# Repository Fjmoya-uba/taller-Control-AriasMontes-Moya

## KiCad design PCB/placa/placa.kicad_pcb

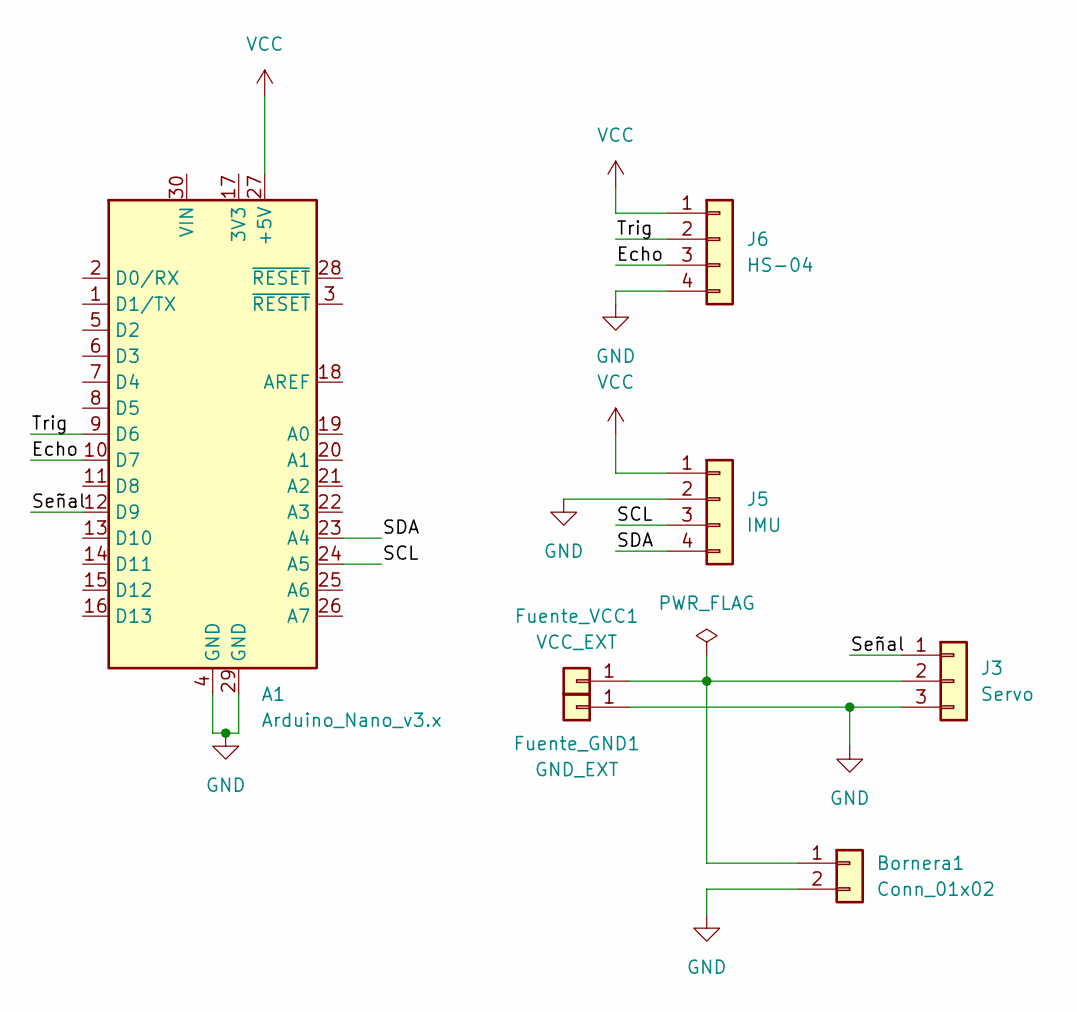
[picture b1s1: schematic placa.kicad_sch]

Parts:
A1: Arduino_Nano_v3.x; Arduino_Nano
Bornera1: Conn_01x02; TerminalBlock_Phoenix_MKDS-1,5-2-5.08_1x02_P5.08mm_Horizont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
Fuente_GND1: GND_EXT; PinHeader_1x01_P2.54mm_Vertical
Fuente_VCC1: VCC_EXT; PinHeader_1x01_P2.54mm_Vertical
J3: Servo; PinHeader_1x03_P2.54mm_Vertical
J5: IMU; PinHeader_1x04_P2.54mm_Vertical
J6: HS-04; PinHeader_1x04_P2.54mm_Vertical

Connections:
/Echo: A1.10 (D7), J6.3
/SCL: A1.24 (A5), J5.3
/SDA: A1.23 (A4), J5.4
/Señal: A1.12 (D9), J3.1
/Trig: A1.9 (D6), J6.2
GND: A1.4 (GND), A1.29 (GND), Bornera1.2, Fuente_GND1.1 (Pin_1_1), J3.3, J5.2, J6.4
unnamed: Bornera1.1, Fuente_VCC1.1 (Pin_1_1), J3.2
VCC: A1.27 (+5V), J5.1, J6.1

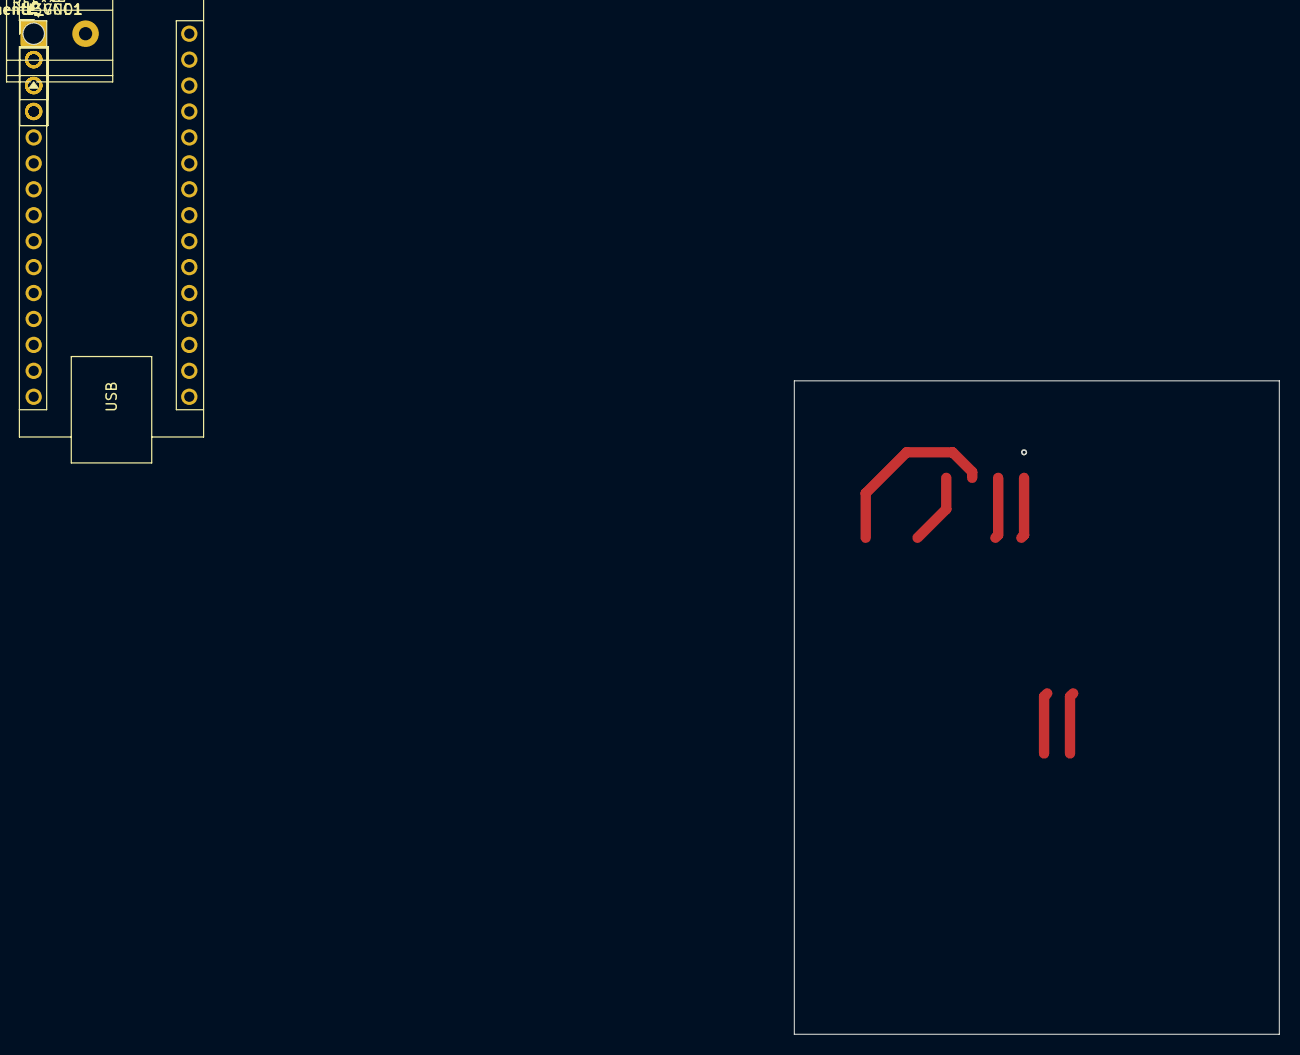
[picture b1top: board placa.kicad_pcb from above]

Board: 2 copper layers, 47.5 x 64.0 mm, 7 parts (0 on the bottom side), 8 nets.
